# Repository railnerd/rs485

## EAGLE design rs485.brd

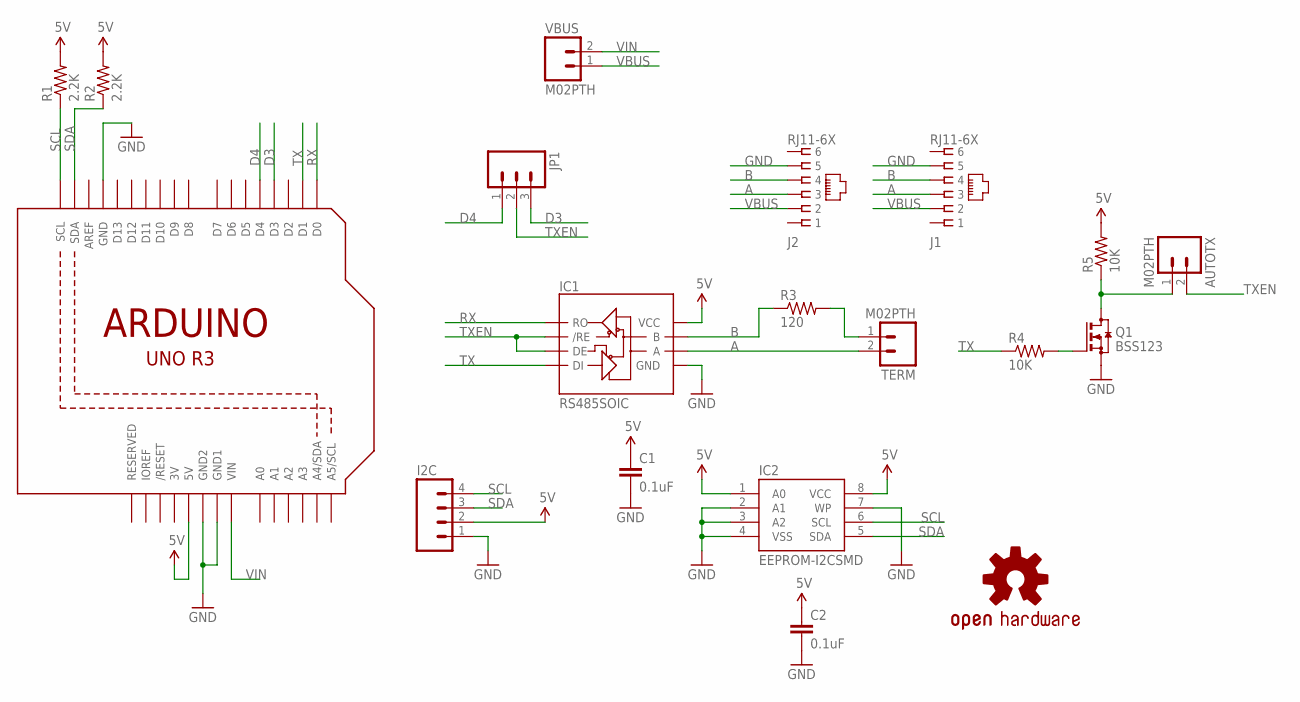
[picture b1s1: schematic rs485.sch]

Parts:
AUTOTX: M02PTH; 1X02
C1, C2: 0.1uF; 0603-CAP
I2C: M04PTH; 1X04
IC1: RS485SOIC; SO08
IC2: EEPROM-I2CSMD; SO08
J1, J2: RJ11-6X; RJ11-NO_SHIELD
JP1: M03PTH; 1X03
LOGO1: OSHW-LOGOL; OSHW-LOGO-L
Q1: BSS123; SOT23
R1, R2: 2.2K; 0603-RES
R3: 120; 0603-RES
R4, R5: 10K; 0603-RES
TERM: M02PTH; 1X02
U1: ARDUINOR3-JUSTPINS; ARDUINOR3
VBUS: M02PTH; 1X02

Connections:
3V: U1.3V
5V: C1.1, C2.1, I2C.2, IC1.8 (VCC), IC2.1 (A0), IC2.8 (VCC), R1.2, R2.2, R5.2, U1.5V
A: IC1.6 (A), J1.3, J2.3, TERM.2
B: IC1.7 (B), J1.4, J2.4, R3.1
D3: JP1.3, U1.D3
D4: JP1.1, U1.D4
GND: C1.2, C2.2, I2C.1, IC1.5 (GND), IC2.2 (A1), IC2.3 (A2), IC2.4 (VSS), IC2.7 (WP), J1.5, J2.5, Q1.2 (S), U1.GND, U1.GND1, U1.GND2
unnamed: R3.2, TERM.1
unnamed: AUTOTX.1, Q1.3 (D), R5.1
unnamed: Q1.1 (G), R4.2
RX: IC1.1 (RO), U1.D0
SCL: I2C.4, IC2.6 (SCL), R1.1, U1.SCL
SDA: I2C.3, IC2.5 (SDA), R2.1, U1.SDA
TX: IC1.4 (DI), R4.1, U1.D1
TXEN: AUTOTX.2, IC1.2 (/RE), IC1.3 (DE), JP1.2
VBUS: J1.2, J2.2, VBUS.1
VIN: U1.VIN, VBUS.2

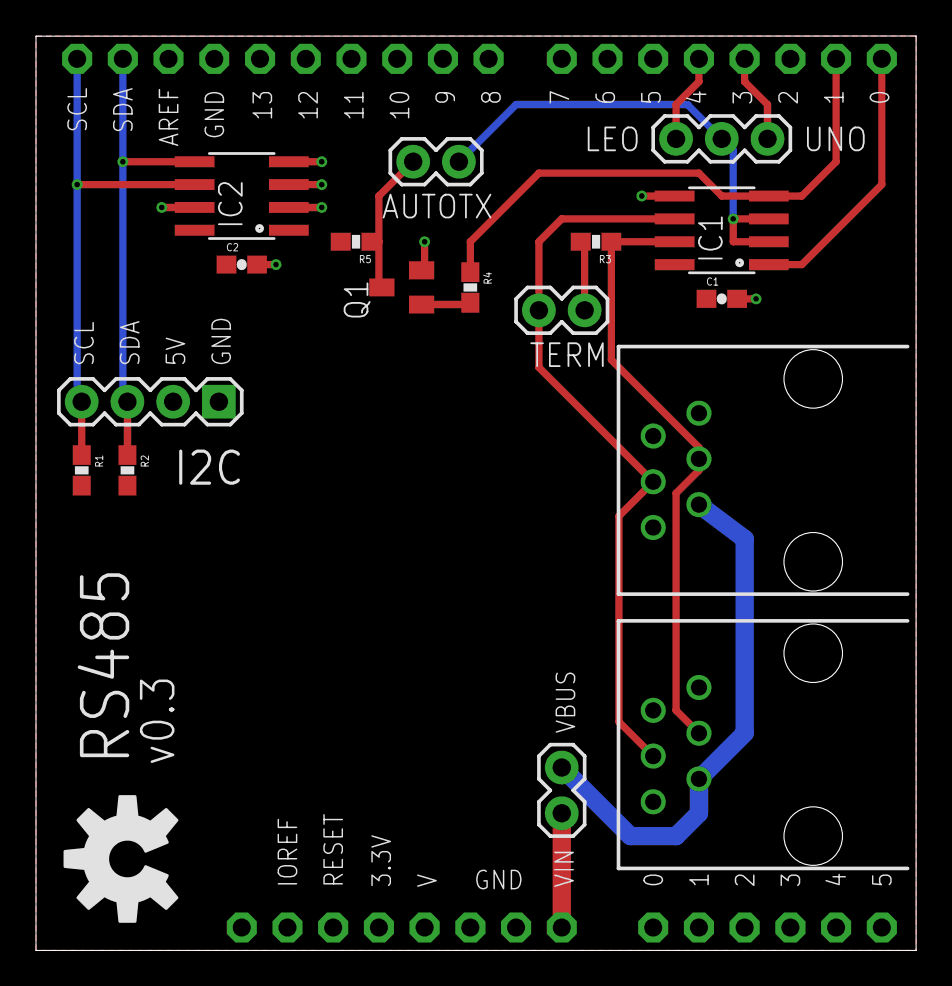
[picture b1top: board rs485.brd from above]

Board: 4 copper layers, 48.9 x 50.8 mm, 19 parts (0 on the bottom side), 16 nets.

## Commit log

2014-05-13 corrected errant 6p6c jacks

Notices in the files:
parts and their libraries:
SparkFun-DigitalIC: Licensing: CC v3.0 Share-Alike You are welcome to use this library for commercial purposes.
